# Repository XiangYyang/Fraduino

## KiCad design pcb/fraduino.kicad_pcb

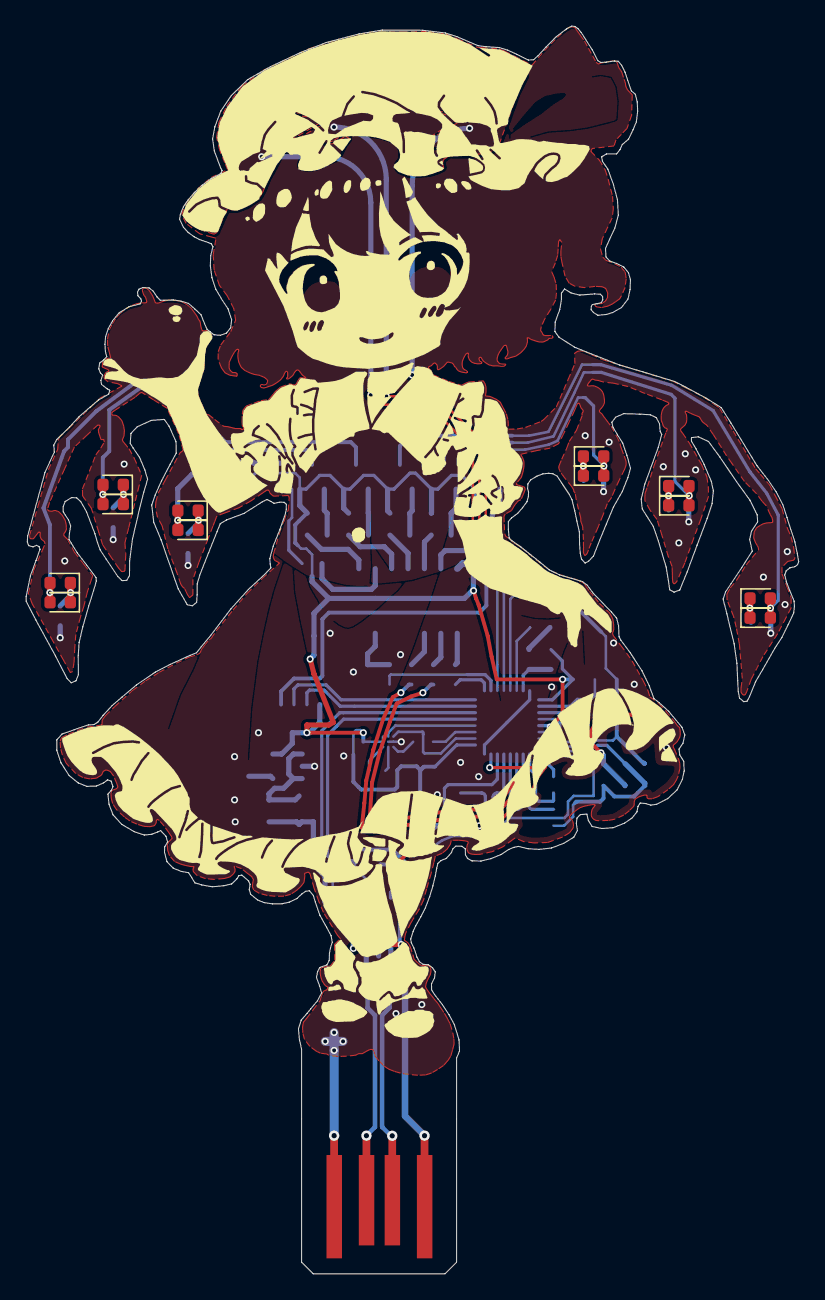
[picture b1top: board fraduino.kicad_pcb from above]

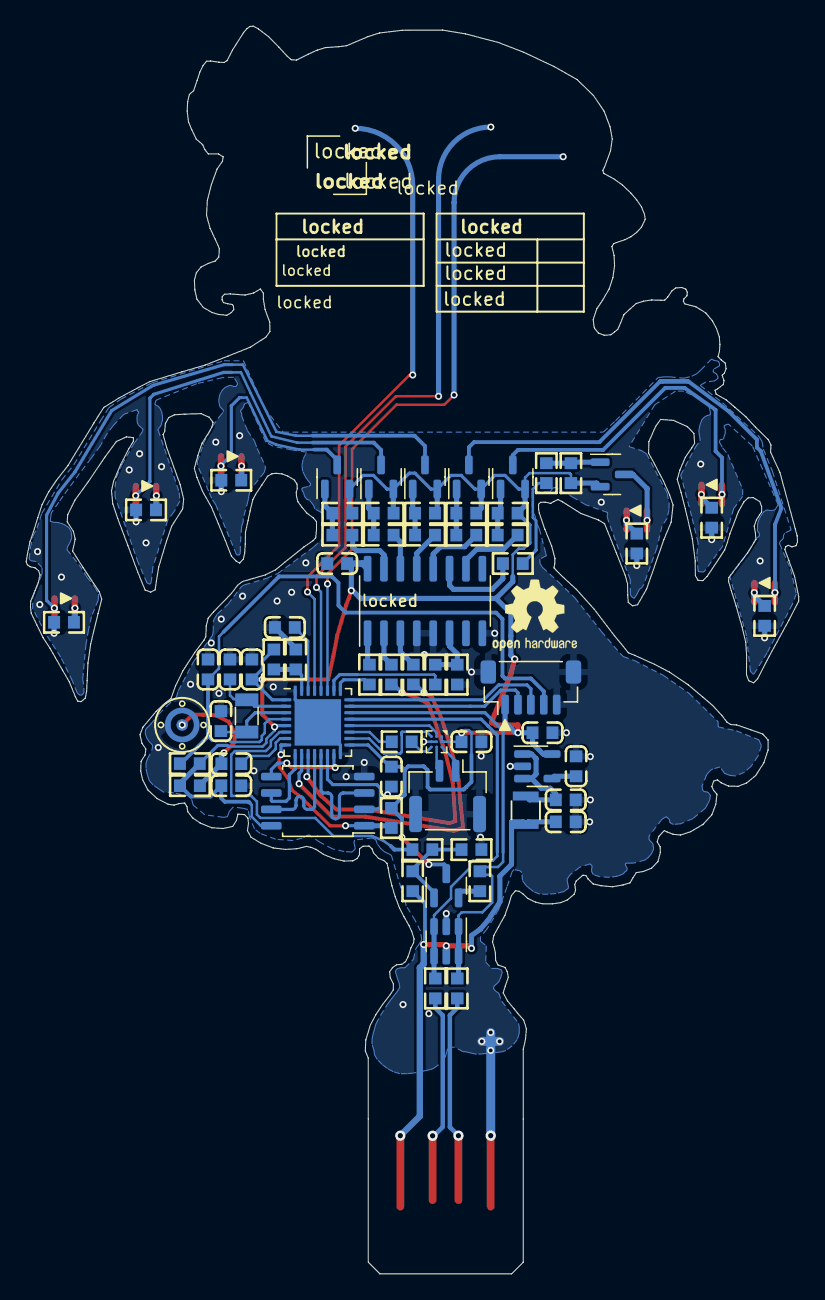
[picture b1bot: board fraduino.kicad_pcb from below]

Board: 2 copper layers, 59.8 x 96.6 mm, 82 parts (69 on the bottom side), 66 nets.

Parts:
C1: locked; 0603_C
C2, C5, C6, C7, C8, C10, C11, C13: 1uF; 0603_C
C3, C4: 12pF; 0603_C
C9, C14: 1nF; 0603_C
C12: 2.2uF; 0603_C
D1, D2, D3, D4, D5, D6, D7, D8, D9, D10, D11, D12: LED; LED_0603_1608Metric
J1: USB_A_Board; USB_TypeA_OnBoard
J2: GH1.25x2; JST_GH_BM02B-GHS-TBT_1x02-1MP_P1.25mm_Vertical
J3: SH1.0x5; JST_SH_BM05B-SRSS-TB_1x05-1MP_P1.00mm_Vertical
L1: 10uH; Inductor_L2.5mm_W2.0mm
MK1: 4013; MIC_4013
Q1, Q3, Q4, Q5, Q6: SS8550; SOT-23
Q2: locked; SOT-23
Q7: SS8050; SOT-23
R1, R2, R4, R8, R10, R11, R13, R14, R16, R17, R20, R23, R37: 10K; 0603_R
R3, R9, R12, R15, R18: 2.2R; 0603_R
R5, R6, R7, R19, R24, R25, R26, R30, R31: locked; 0603_R
R21: N.C.; 0603_R
R22: 100K; 0603_R
R27, R28, R29: 22R; 0603_R
R32: 36K; 0603_R
R33: 100R; 0603_R
R34: 0R; 0603_R
R44: 2.2K; 0603_R
Sym1: Logo_Open_Hardware_Large; OSHW-Logo2_7.3x6mm_SilkScreen
U1: STM32L432KBU6; QFN-32-1EP_5x5mm_P0.5mm_EP3.6x3.6mm
U2: W25Q32JVSS; SOIC-8_5.23x5.23mm_P1.27mm
U3: 74LS138; SOP-16_3.9x9.9mm_P1.27mm
U4: SRV05-4; SOT-23-6
U5: MAX98357AEWL+T; WLCSP-9_3x3_1.437x1.347mm
U6: TPS79333; SOT-23-5
Y1: 32.768kHz; Crystal_SMD_3215-2Pin_3.2x1.5mm

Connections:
+3.3V: C1.1, C2.1, C7.1, C8.1, C10.1, C11.1, J3.1, Q1.2 (E), Q2.2 (E), Q3.2 (E), Q4.2 (E), Q5.2 (E), Q6.2 (E), Q7.3 (C), R2.2, R5.2, R8.2, R11.2, R14.2, R17.2, R21.1, R23.1, R37.2, R44.1, U1.1 (VDD), U1.5 (VDDA/REF+), U1.17 (VDD), U2.8 (VCC), U3.16 (VCC), U5.A1 (SD_MODE), U5.A2 (VDD), U6.5 (OUT)
/板板/D+: R24.1, R30.2, U1.22 (PA12), U4.1 (IO1), U4.6 (IO4)
/板板/D-: R25.2, U1.21 (PA11), U4.3 (IO2), U4.4 (IO3)
/板板/LED_A: R3.1, U3.12 (O3)
/板板/LED_B: R6.1, U3.10 (O5)
/板板/LED_C: R9.1, R19.1
/板板/LED_D: R12.1, U3.15 (O0)
/板板/LED_E: R15.1, U3.14 (O1)
/板板/LED_F: R18.1, U3.13 (O2)
/板板/LED_PWM: R29.2, U1.26 (PB3)
/板板/LED_SEL_A: R26.2, U1.25 (PA15)
/板板/LED_SEL_B: R27.2, U1.11 (PA5)
/板板/LED_SEL_C: R28.2, U1.10 (PA4)
/板板/MIC: C9.2, U1.7 (PA1)
/板板/OSC32_N: C3.2, U1.2 (PC14/OSC32_IN), Y1.1
/板板/OSC32_P: C4.2, U1.3 (PC15/OSC32_OUT), Y1.2
/板板/QSPI_CLK: U1.9 (PA3), U2.6 (CLK)
/板板/QSPI_IO0: U1.15 (PB1), U2.5 (DI(IO0))
/板板/QSPI_IO1: U1.14 (PB0), U2.2 (DO(IO1))
/板板/QSPI_IO2: U1.13 (PA7), U2.3 (IO2)
/板板/QSPI_IO3: U1.12 (PA6), U2.7 (IO3)
/板板/QSPI_~CS: R37.1, U1.8 (PA2), U2.1 (~CS)
/板板/SAI_FS: R34.2, U1.19 (PA9)
/板板/SAI_SCK: U1.18 (PA8), U5.C1 (BCLK)
/板板/SAI_SD: U1.20 (PA10), U5.B1 (DIN)
/板板/SWCLK: J3.3, U1.24 (PA14)
/板板/SWDIO: J3.2, U1.23 (PA13)
/板板/TSC_IO4: C14.1, U1.30 (PB7)
/板板/USB_RE_ENUM: R33.1, U1.6 (PA0/CK_IN)
/板板/U_D+: J1.3 (D+), R24.2
/板板/U_D-: J1.2 (D-), R25.1
/板板/~RST: C5.1, J3.4, R23.2, U1.4 (~RST)
GND: C1.2, C2.2, C3.1, C4.1, C5.2, C6.1, C7.2, C8.2, C10.2, C11.2, C12.2, C13.2, C14.2, J1.4 (GND), J2.MP (MountPin), J3.5, J3.MP (MountPin), MK1.1 (-), R1.2, R4.2, R7.2, R10.2, R13.2, R16.2, R20.2, R22.1, R32.2, U1.16 (VSS), U1.32 (VSS), U1.33 (PAD), U2.4 (GND), U3.4 (E1), U3.5 (E2), U3.8 (GND), U4.2 (VN), U5.B2 (GAIN-SOLT), U5.C2 (GND), U6.2 (GND)
unnamed: D1.2 (A), D2.2 (A), Q1.3 (C)
unnamed: D1.1 (K), D2.1 (K), R1.1
unnamed: D3.2 (A), D4.2 (A), Q2.3 (C)
unnamed: D3.1 (K), D4.1 (K), R4.1
unnamed: D5.2 (A), D6.2 (A), Q3.3 (C)
unnamed: D5.1 (K), D6.1 (K), R7.1
unnamed: D7.2 (A), D8.2 (A), Q4.3 (C)
unnamed: D7.1 (K), D8.1 (K), R10.1
unnamed: D9.2 (A), D10.2 (A), Q5.3 (C)
unnamed: D9.1 (K), D10.1 (K), R13.1
unnamed: D11.2 (A), D12.2 (A), Q6.3 (C)
unnamed: D11.1 (K), D12.1 (K), R16.1
unnamed: J2.1, U5.A3 (OUTP)
unnamed: J2.2, U5.B3 (OUTN)
unnamed: C9.1, MK1.2 (+), R44.2
unnamed: Q1.1 (B), R2.1, R3.2
unnamed: Q2.1 (B), R5.1, R6.2
unnamed: Q3.1 (B), R8.1, R9.2
unnamed: Q4.1 (B), R11.1, R12.2
unnamed: Q5.1 (B), R14.1, R15.2
unnamed: Q6.1 (B), R17.1, R18.2
unnamed: Q7.1 (B), R31.2, R32.1, R33.2
unnamed: Q7.2 (E), R30.1
unnamed: R21.2, R22.2, U1.31 (PH3/BOOT0)
unnamed: R26.1, U3.1 (A0)
unnamed: R27.1, U3.2 (A1)
unnamed: R28.1, U3.3 (A2)
unnamed: R20.1, R29.1, U3.6 (E3)
unnamed: R19.2, U3.11 (O4)
unnamed: R34.1, U5.C3 (LRCLK)
unnamed: C12.1, U6.4 (BYP)
unnamed: C13.1, L1.2, U6.1 (IN), U6.3 (EN)
USB_VBUS: C6.2, J1.1 (VBUS), L1.1, R31.1, U4.5 (VP)

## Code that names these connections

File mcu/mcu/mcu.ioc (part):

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Mcu.Name=STM32L432K(B-C)Ux
Mcu.Package=UFQFPN32
Mcu.UserName=STM32L432KBUx
PA0.GPIOParameters=GPIO_Label
PA0.GPIO_Label=USB_REENUM_PIN
PA0.Signal=GPIO_Output
PA1.Signal=SharedAnalog_PA1
PA10.Mode=SAI_A_Master
PA10.Signal=SAI1_SD_A
PA11.Mode=Device
PA11.Signal=USB_DM
PA12.Mode=Device
PA12.Signal=USB_DP
PA13\ (JTMS-SWDIO).Mode=Serial_Wire
PA13\ (JTMS-SWDIO).Signal=SYS_JTMS-SWDIO
PA14\ (JTCK-SWCLK).Mode=Serial_Wire
PA14\ (JTCK-SWCLK).Signal=SYS_JTCK-SWCLK
PA15\ (JTDI).Signal=GPIO_Output
PA2.Mode=Single Bank 1
PA2.Signal=QUADSPI_BK1_NCS
PA3.Mode=Single Bank 1
PA3.Signal=QUADSPI_CLK
PA4.Signal=GPIO_Output
PA5.Signal=GPIO_Output
PA6.Mode=Single Bank 1
PA6.Signal=QUADSPI_BK1_IO3
PA7.Mode=Single Bank 1
PA7.Signal=QUADSPI_BK1_IO2
PA8.Mode=SAI_A_Master
PA8.Signal=SAI1_SCK_A
PA9.Mode=SAI_A_Master
PA9.Signal=SAI1_FS_A
PB0.Mode=Single Bank 1
PB0.Signal=QUADSPI_BK1_IO1
PB1.Mode=Single Bank 1
PB1.Signal=QUADSPI_BK1_IO0
PB3\ (JTDO-TRACESWO).Signal=S_TIM2_CH2
PB4\ (NJTRST).Mode=G2_IO1-Channel
PB4\ (NJTRST).Signal=TSC_G2_IO1
PB5.Mode=G2_IO2-Channel
PB5.Signal=TSC_G2_IO2
PB6.Mode=G2_IO3-Channel
PB6.Signal=TSC_G2_IO3
PB7.Mode=G2_IO4-Sampling
PB7.Signal=TSC_G2_IO4
PC14-OSC32_IN\ (PC14).Mode=LSE-External-Oscillator
PC14-OSC32_IN\ (PC14).Signal=RCC_OSC32_IN
PC15-OSC32_OUT\ (PC15).Mode=LSE-External-Oscillator
PC15-OSC32_OUT\ (PC15).Signal=RCC_OSC32_OUT
RCC.HSE_VALUE=8000000
RCC.SYSCLKFreq_VALUE=80000000
RCC.SYSCLKSource=RCC_SYSCLKSOURCE_PLLCLK
board=custom

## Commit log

2023-04-11 add: rust的内容
2023-06-21 chg: 第一版投产
2023-06-26 add: makefile;
2023-06-27 add: 一系列东东
